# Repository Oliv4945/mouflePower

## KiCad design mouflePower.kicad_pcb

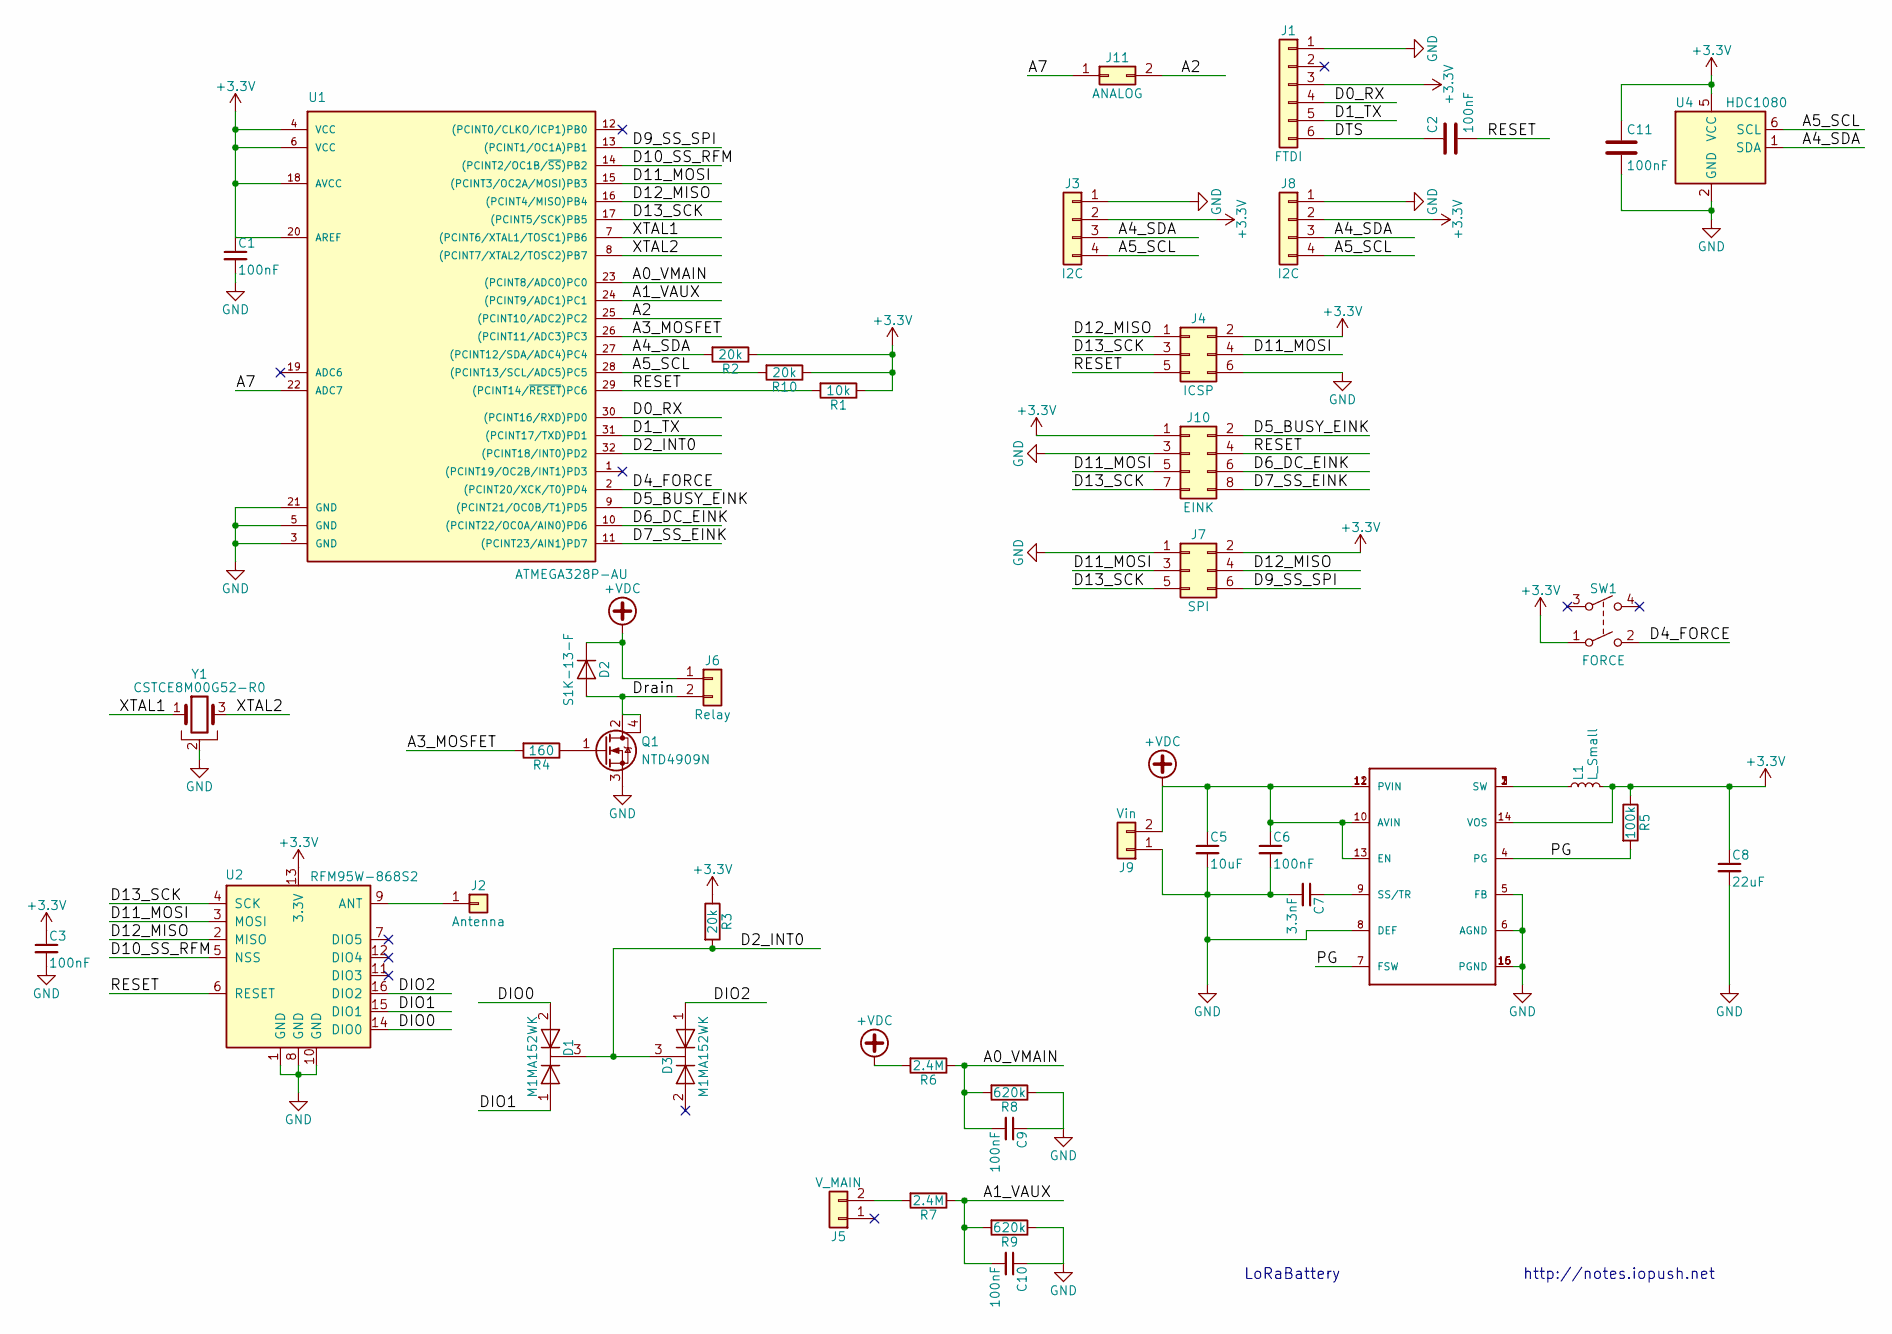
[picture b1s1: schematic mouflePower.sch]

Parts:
C1, C2, C3, C6, C9, C10, C11: 100nF; C_0805_2012Metric
C5: 10uF; C_0805_2012Metric
C7: 3.3nF; C_0805_2012Metric
C8: 22uF; C_0805_2012Metric
D1, D3: M1MA152WK; SC-59_Handsoldering
D2: S1K-13-F; D_SMA
J1: FTDI; PinHeader_1x06_P2.54mm_Vertical
J2: Antenna; PinHeader_1x01_P2.54mm_Vertical
J3, J8: I2C; PinHeader_1x04_P2.54mm_Vertical
J4: ICSP; PinHeader_2x03_P2.54mm_Vertical
J5: V_MAIN; TerminalBlock_Phoenix_MKDS-1,5-2_1x02_P5.00mm_Horizontal
J6: Relay; TerminalBlock_Phoenix_MKDS-1,5-2_1x02_P5.00mm_Horizontal
J7: SPI; PinHeader_2x03_P2.54mm_Vertical
J9: Vin; TerminalBlock_Phoenix_MKDS-1,5-2_1x02_P5.00mm_Horizontal
J10: EINK; PinHeader_2x04_P2.54mm_Vertical
J11: ANALOG; PinHeader_1x02_P2.54mm_Vertical
L1: L_Small; L_Vishay_IHLP-1212
Q1: NTD4909N; CASE-369AA
R1: 10k; R_0805_2012Metric
R2, R3, R10: 20k; R_0805_2012Metric
R4: 160; R_0805_2012Metric
R5: 100k; R_0805_2012Metric
R6, R7: 2.4M; R_0805_2012Metric
R8, R9: 620k; R_0805_2012Metric
SW1: FORCE; SW_TH_Tactile_Omron_B3F-10xx
U1: ATMEGA328P-AU; TQFP-32_7x7mm_P0.8mm
U2: RFM95W-868S2; Hopref_RFM9XW_SMD
U3: PMIC-TPS62132RGTR(QFN16); QFN16G-0.5-3X3MM
U4: HDC1080; Texas_PWSON-N6
Y1: CSTCE8M00G52-R0; X3-SMD-3.6X1.3X0.8MM

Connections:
+3V3: C1.1, C3.1, C8.1, C11.1, J1.3, J3.2, J4.2, J7.2, J8.2, J10.1, L1.2, R1.1, R2.1, R3.1, R5.1, R10.1, SW1.1, U1.4 (VCC), U1.6 (VCC), U1.18 (AVCC), U1.20 (AREF), U2.13 (3.3V), U3.14 (VOS), U4.5 (VCC)
+VDC: C5.1, C6.1, D2.1 (K), J6.1, J9.2, R6.2, U3.10 (AVIN), U3.11 (PVIN), U3.12 (PVIN), U3.13 (EN)
/A0_VMAIN: C9.2, R6.1, R8.2, U1.23 ((PCINT8/ADC0)PC0)
/A1_VAUX: C10.2, R7.1, R9.2, U1.24 ((PCINT9/ADC1)PC1)
/A2: J11.2, U1.25 ((PCINT10/ADC2)PC2)
/A3_MOSFET: R4.2, U1.26 ((PCINT11/ADC3)PC3)
/A4_SDA: J3.3, J8.3, R2.2, U1.27 ((PCINT12/SDA/ADC4)PC4), U4.1 (SDA)
/A5_SCL: J3.4, J8.4, R10.2, U1.28 ((PCINT13/SCL/ADC5)PC5), U4.6 (SCL)
/A7: J11.1, U1.22 (ADC7)
/D0_RX: J1.4, U1.30 ((PCINT16/RXD)PD0)
/D1_TX: J1.5, U1.31 ((PCINT17/TXD)PD1)
/D2_INT0: D1.3 (K), D3.3 (K), R3.2, U1.32 ((PCINT18/INT0)PD2)
/D4_FORCE: SW1.2, U1.2 ((PCINT20/XCK/T0)PD4)
/D5_BUSY_EINK: J10.2, U1.9 ((PCINT21/OC0B/T1)PD5)
/D6_DC_EINK: J10.6, U1.10 ((PCINT22/OC0A/AIN0)PD6)
/D7_SS_EINK: J10.8, U1.11 ((PCINT23/AIN1)PD7)
/D9_SS_SPI: J7.6, U1.13 ((PCINT1/OC1A)PB1)
/D10_SS_RFM: U1.14 ((PCINT2/OC1B/~SS~)PB2), U2.5 (NSS)
/D11_MOSI: J4.4, J7.3, J10.5, U1.15 ((PCINT3/OC2A/MOSI)PB3), U2.3 (MOSI)
/D12_MISO: J4.1, J7.4, U1.16 ((PCINT4/MISO)PB4), U2.2 (MISO)
/D13_SCK: J4.3, J7.5, J10.7, U1.17 ((PCINT5/SCK)PB5), U2.4 (SCK)
/DIO0: D1.2 (A), U2.14 (DIO0)
/DIO1: D1.1 (A), U2.15 (DIO1)
/DIO2: D3.1 (A), U2.16 (DIO2)
/DTS: C2.1, J1.6
/Drain: D2.2 (A), J6.2, Q1.2 (D), Q1.4 (D)
/PG: R5.2, U3.4 (PG), U3.7 (FSW)
/RESET: C2.2, J4.5, J10.4, R1.2, U1.29 ((PCINT14/~RESET~)PC6), U2.6 (RESET)
/XTAL1: U1.7 ((PCINT6/XTAL1/TOSC1)PB6), Y1.1
/XTAL2: U1.8 ((PCINT7/XTAL2/TOSC2)PB7), Y1.3
GND: C1.2, C3.2, C5.2, C6.2, C7.2, C8.2, C9.1, C10.1, C11.2, J1.1, J3.1, J4.6, J7.1, J8.1, J9.1, J10.3, Q1.3 (S), R8.1, R9.1, U1.3 (GND), U1.5 (GND), U1.21 (GND), U2.1 (GND), U2.8 (GND), U2.10 (GND), U3.5 (FB), U3.6 (AGND), U3.8 (DEF), U3.15 (PGND), U3.16 (PGND), U4.2 (GND), U4.7 (GND), Y1.2
unnamed: C7.1, U3.9 (SS/TR)
unnamed: J2.1, U2.9 (ANT)
unnamed: J5.2, R7.2
unnamed: L1.1, U3.1 (SW), U3.2 (SW), U3.3 (SW)
unnamed: Q1.1 (G), R4.1

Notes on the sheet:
LoRaBattery
http://notes.iopush.net

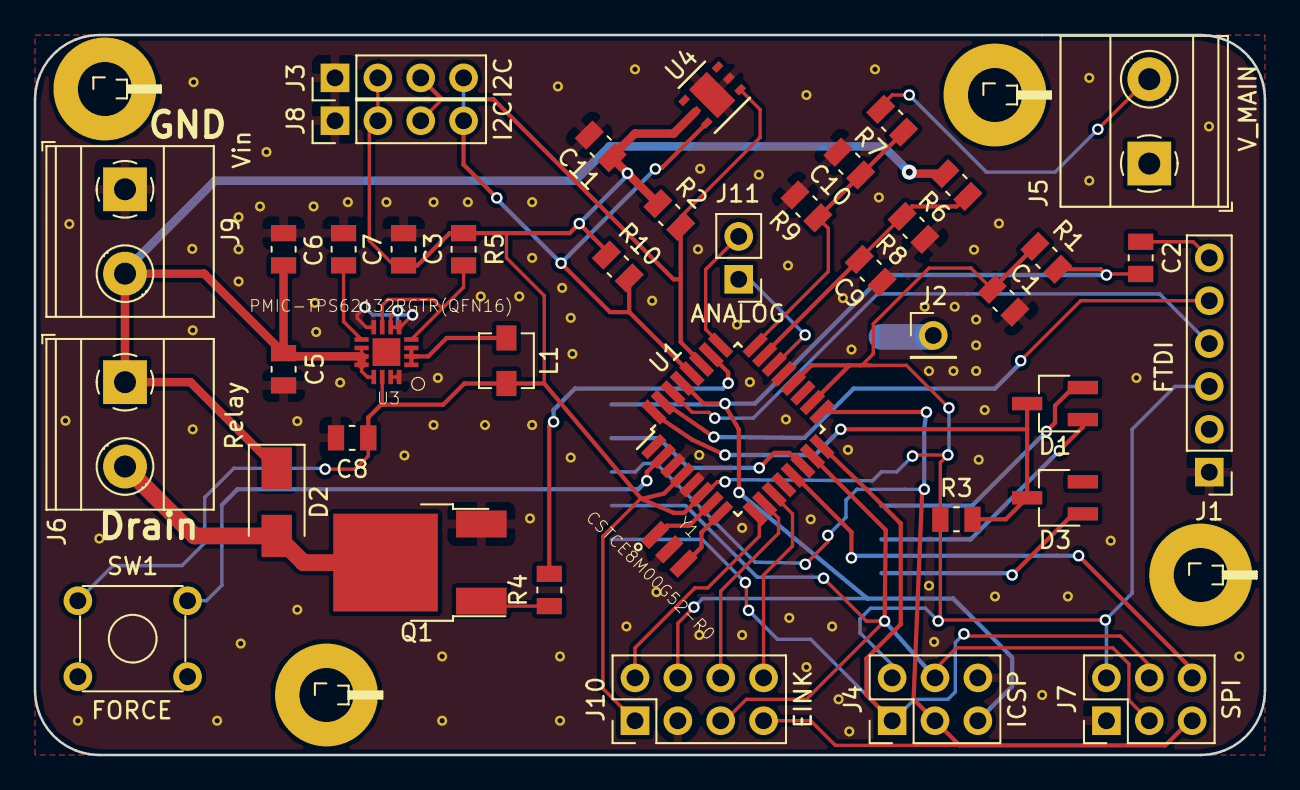
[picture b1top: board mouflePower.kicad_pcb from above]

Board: 2 copper layers, 72.9 x 42.7 mm, 42 parts (1 on the bottom side), 36 nets.

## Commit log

2018-03-14 Add flyback diode
2018-03-17 Change silkscreen
2018-03-17 Add gerbers
2018-03-19 Untrack bak files
2018-03-19 Add gitignore file
2018-03-19 Move KiCad design files to hardware folder
2018-03-19 Software init
2018-04-06 Add BOM file (CSV)
2018-04-06 Add VS Code project file
2018-04-07 ADC pin naming correction
2018-04-07 Select "/dev/ttyUSB*" by default
2018-04-07 Add VAUX calibration value
2018-04-07 Define mosfet states
2018-04-15 Color/uncolored correction
2018-04-15 Add VAUX calibration
2018-04-15 Add display & battery handling
2018-04-15 Refresh screen only if required
2018-04-15 Update threshold
2018-04-25 Use font width
2018-04-30 Add graphical pages
2018-04-30 Add vMain, display state & bug correction
2018-04-30 Change color regarding tension
